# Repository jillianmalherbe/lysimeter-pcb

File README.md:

# lysimeter-pcb
KiCad PCB files for lysimeter system.

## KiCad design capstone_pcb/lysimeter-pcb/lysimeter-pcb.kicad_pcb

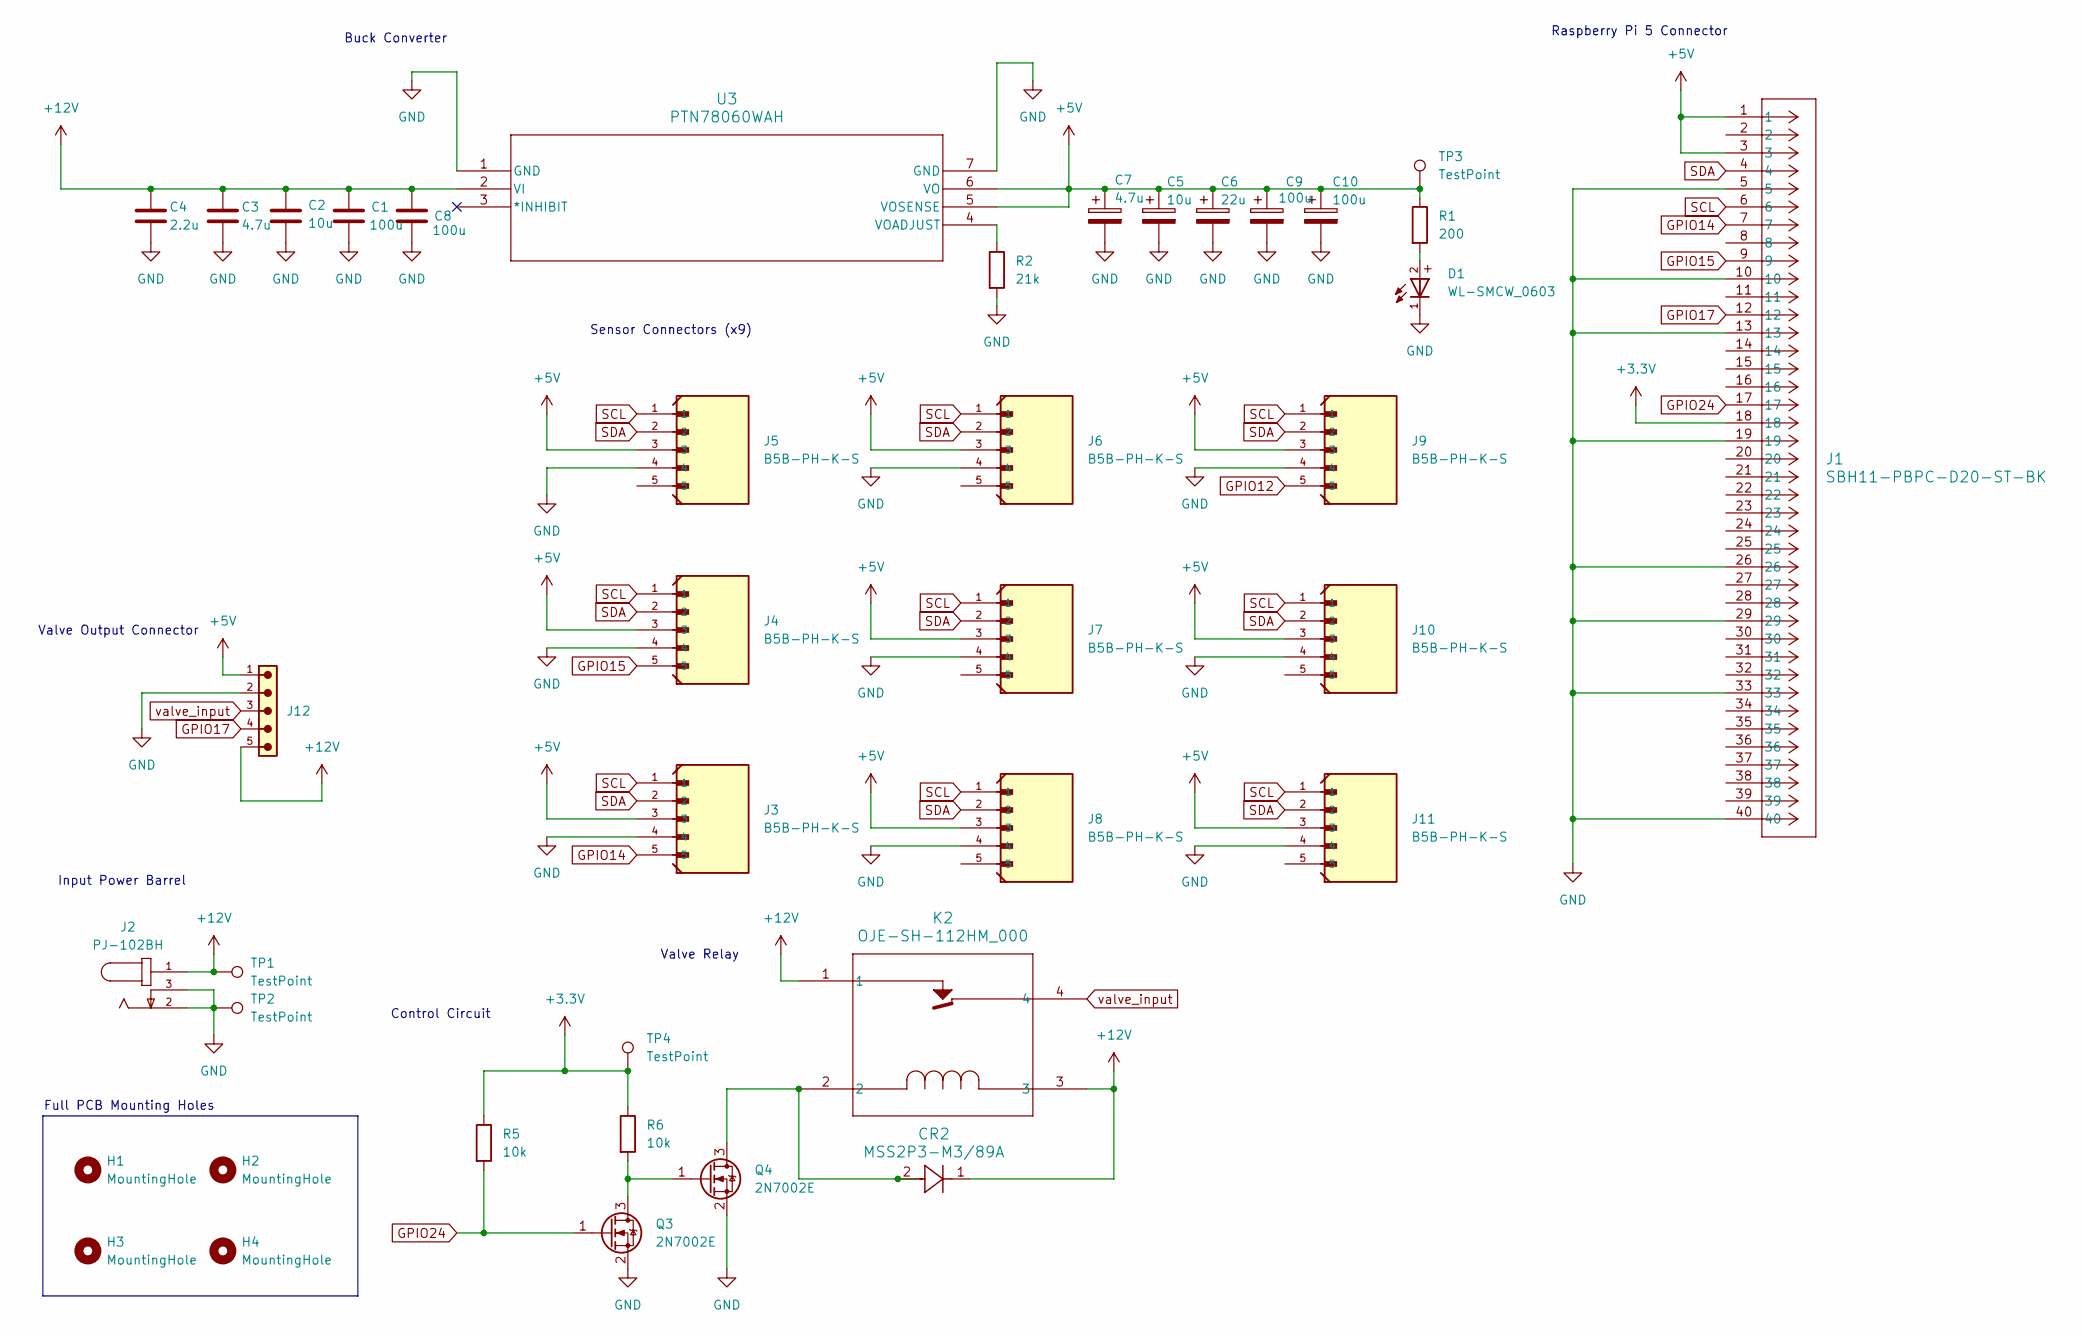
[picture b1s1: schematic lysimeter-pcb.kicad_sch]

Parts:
C1: 100u; C_1206_3216Metric; LCSC 150008
C2, C5: 10u; C_0603_1608Metric_Pad1.08x0.95mm_HandSolder; LCSC C1691
C3, C7: 4.7u; C_0603_1608Metric_Pad1.08x0.95mm_HandSolder; LCSC C1705
C4: 2.2u; C_0603_1608Metric_Pad1.08x0.95mm_HandSolder; LCSC C1607
C6: 22u; C_0603_1608Metric_Pad1.08x0.95mm_HandSolder; LCSC C15500
C8, C9, C10: 100u; C_1206_3216Metric; LCSC 15008
CR2: MSS2P3-M3/89A; DIODE_MSP3V3-L; LCSC C466984
D1: WL-SMCW_0603; WL-SMCW_0603-led; LCSC C2286
H1, H2, H3, H4: MountingHole; MountingHole_2.7mm_Pad
J1: SBH11-PBPC-D20-ST-BK; CONN40_SBH11-PBPC-D20-ST-BK_SUL
J2: PJ-102BH; CUI_PJ-102BH; PART_REV 1.02
J3, J4, J5, J6, J7, J8, J9, J10, J11: B5B-PH-K-S; CONN_B5B-XH-A_JST
J12: 61300511121; 61300511121-5pin; PART-NUMBER 61300511121
K2: OJE-SH-112HM_000; RELAY4_112HM-000_TEC
Q3, Q4: 2N7002E; SOT23_PAN-L; LCSC C350312
R1: 200; R_0603_1608Metric_Pad0.98x0.95mm_HandSolder; LCSC C8218
R2: 21k; R_0603_1608Metric; LCSC C22956
R5, R6: 10k; R_0603_1608Metric_Pad0.98x0.95mm_HandSolder; LCSC C25804
TP1, TP2, TP3, TP4: TestPoint; TestPoint_Pad_D1.5mm
U3: PTN78060WAH; EUW7-buck

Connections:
+3.3V: J1.18, R5.1, R6.1, TP4.1
+5V: C5.1, C6.1, C7.1, C9.1, C10.1, J1.1, J1.3, J3.3, J4.3, J5.3, J6.3, J7.3, J8.3, J9.3, J10.3, J11.3, J12.1, R1.1, TP3.1, U3.5 (VOSENSE), U3.6 (VO)
+12V: C1.1, C2.1, C3.1, C4.1, C8.1, CR2.1, J2.1, J12.5, K2.1, K2.3, TP1.1, U3.2 (VI)
GND: C1.2, C2.2, C3.2, C4.2, C5.2, C6.2, C7.2, C8.2, C9.2, C10.2, D1.1, J1.5, J1.10, J1.13, J1.19, J1.26, J1.29, J1.33, J1.40, J2.2, J2.3, J3.4, J4.4, J5.4, J6.4, J7.4, J8.4, J9.4, J10.4, J11.4, J12.2, Q3.2 (S), Q4.2 (S), R2.2, TP2.1, U3.1 (GND), U3.7 (GND)
GPIO12: J9.5
GPIO14: J1.7, J3.5
GPIO15: J1.9, J4.5
GPIO17: J1.12, J12.4
GPIO24: J1.17, Q3.1 (G), R5.2
unnamed: D1.2, R1.2
unnamed: Q3.3 (D), Q4.1 (G), R6.2
unnamed: CR2.2, K2.2, Q4.3 (D)
unnamed: R2.1, U3.4 (VOADJUST)
SCL: J1.6, J3.1, J4.1, J5.1, J6.1, J7.1, J8.1, J9.1, J10.1, J11.1
SDA: J1.4, J3.2, J4.2, J5.2, J6.2, J7.2, J8.2, J9.2, J10.2, J11.2
valve_input: J12.3, K2.4

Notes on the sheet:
Valve Output Connector
Valve Relay
Control Circuit
Buck Converter
Raspberry Pi 5 Connector
Full PCB Mounting Holes
Input Power Barrel
Sensor Connectors (x9)

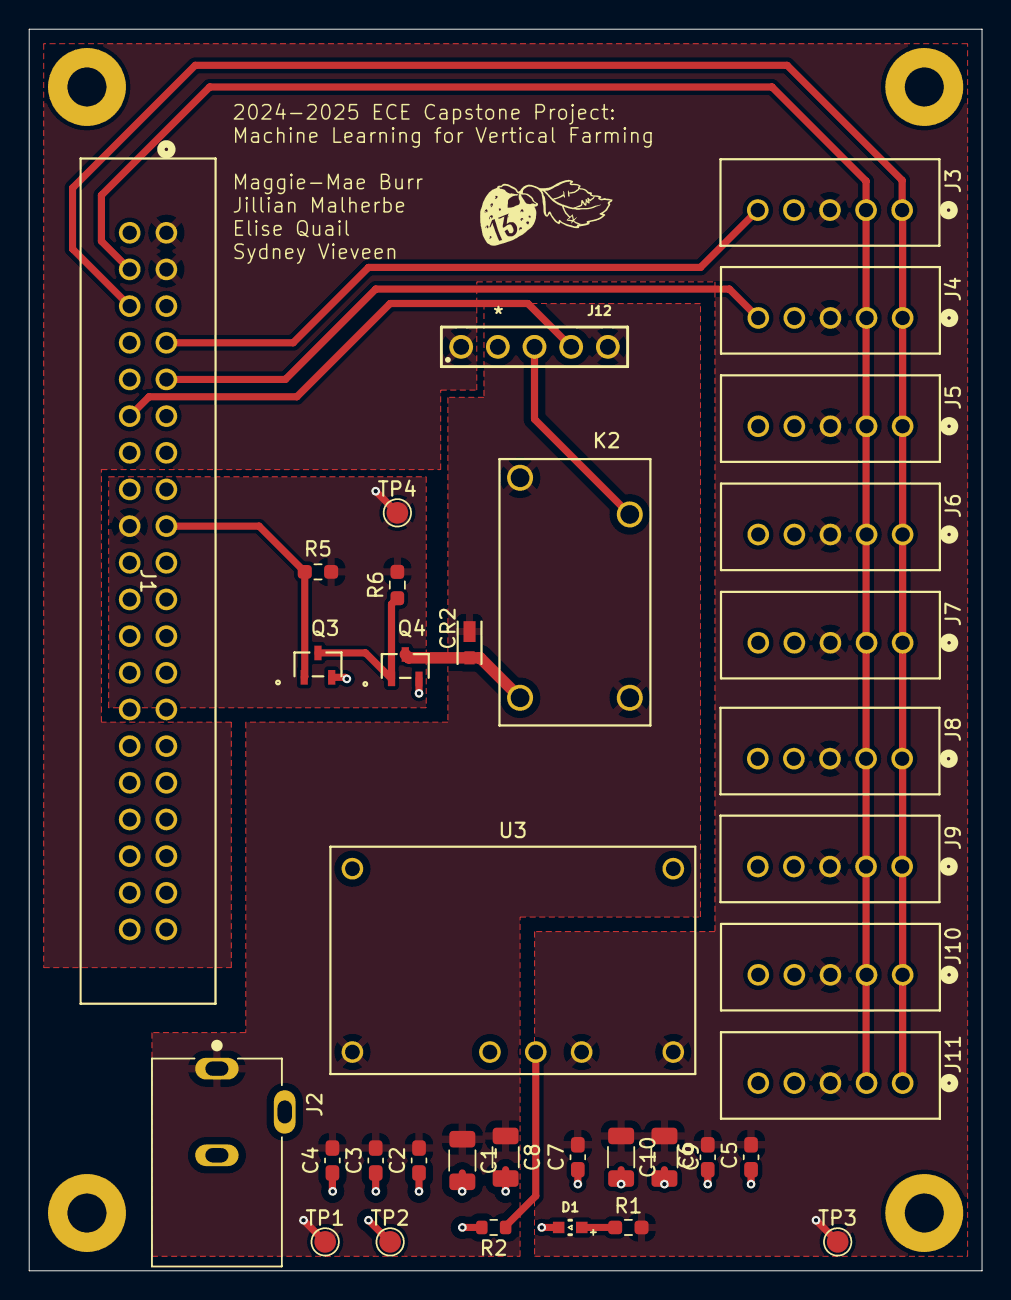
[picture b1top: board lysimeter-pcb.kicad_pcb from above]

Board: 2 copper layers, 66.0 x 86.0 mm, 40 parts (0 on the bottom side), 15 nets.

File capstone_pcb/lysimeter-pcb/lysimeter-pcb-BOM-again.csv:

"Reference","Value","Datasheet","Footprint","Qty","DNP","LCSC"
"C1,C8,C9,C10","100u","~","Capacitor_SMD:C_1206_3216Metric","4","","-- mixed values --"
"C2,C5","10u","~","Capacitor_SMD:C_0603_1608Metric_Pad1.08x0.95mm_HandSolder","2","","C1691"
"C3,C7","4.7u","~","Capacitor_SMD:C_0603_1608Metric_Pad1.08x0.95mm_HandSolder","2","","C1705"
"C4","2.2u","~","Capacitor_SMD:C_0603_1608Metric_Pad1.08x0.95mm_HandSolder","1","","C1607"
"C6","22u","~","Capacitor_SMD:C_0603_1608Metric_Pad1.08x0.95mm_HandSolder","1","",""
"CR2","MSS2P3-M3/89A","MSS2P3-M3/89A","lysimeter_footprints:DIODE_MSP3V3-L","1","","C466984"
"D1","WL-SMCW_0603","","lysimeter_footprints:WL-SMCW_0603-led","1","","C2286"
"J1","SBH11-PBPC-D20-ST-BK","SBH11-PBPC-D20-ST-BK","CONN40_SBH11-PBPC-D20-ST-BK_SUL","1","",""
"J2","PJ-102BH","","CUI_PJ-102BH","1","",""
"J3,J4,J5,J6,J7,J8,J9,J10,J11","B5B-PH-K-S","","lysimeter_footprints:CONN_B5B-XH-A_JST","9","",""
"J12","61300511121","","lysimeter_footprints:61300511121-5pin","1","",""
"K2","OJE-SH-112HM_000","OJE-SH-112HM_000","lysimeter_footprints:RELAY4_112HM-000_TEC","1","",""
"Q3,Q4","2N7002E","http://www.diodes.com/assets/Datasheets/ds30376.pdf","lysimeter_footprints:SOT23_PAN-L","2","","C350312"
"R1","200","~","Resistor_SMD:R_0603_1608Metric_Pad0.98x0.95mm_HandSolder","1","","C8218"
"R2","21k","~","Resistor_SMD:R_0603_1608Metric","1","","C22956"
"R5,R6","10k","~","Resistor_SMD:R_0603_1608Metric_Pad0.98x0.95mm_HandSolder","2","","C25804"
"TP1,TP2,TP3,TP4","TestPoint","~","TestPoint:TestPoint_Pad_D1.5mm","4","",""
"U3","PTN78060WAH","PTN78060WAH","lysimeter_footprints:EUW7-buck","1","",""

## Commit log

2025-05-01 Adding initial files from capstone project.
2025-08-29 repository reorganising
2025-08-29 reorganisation
2025-08-29 remove local and global
2025-08-29 adding global and local pcbs
2025-08-29 global_pcb: schematic
2025-08-29 local_pcb: deleter
